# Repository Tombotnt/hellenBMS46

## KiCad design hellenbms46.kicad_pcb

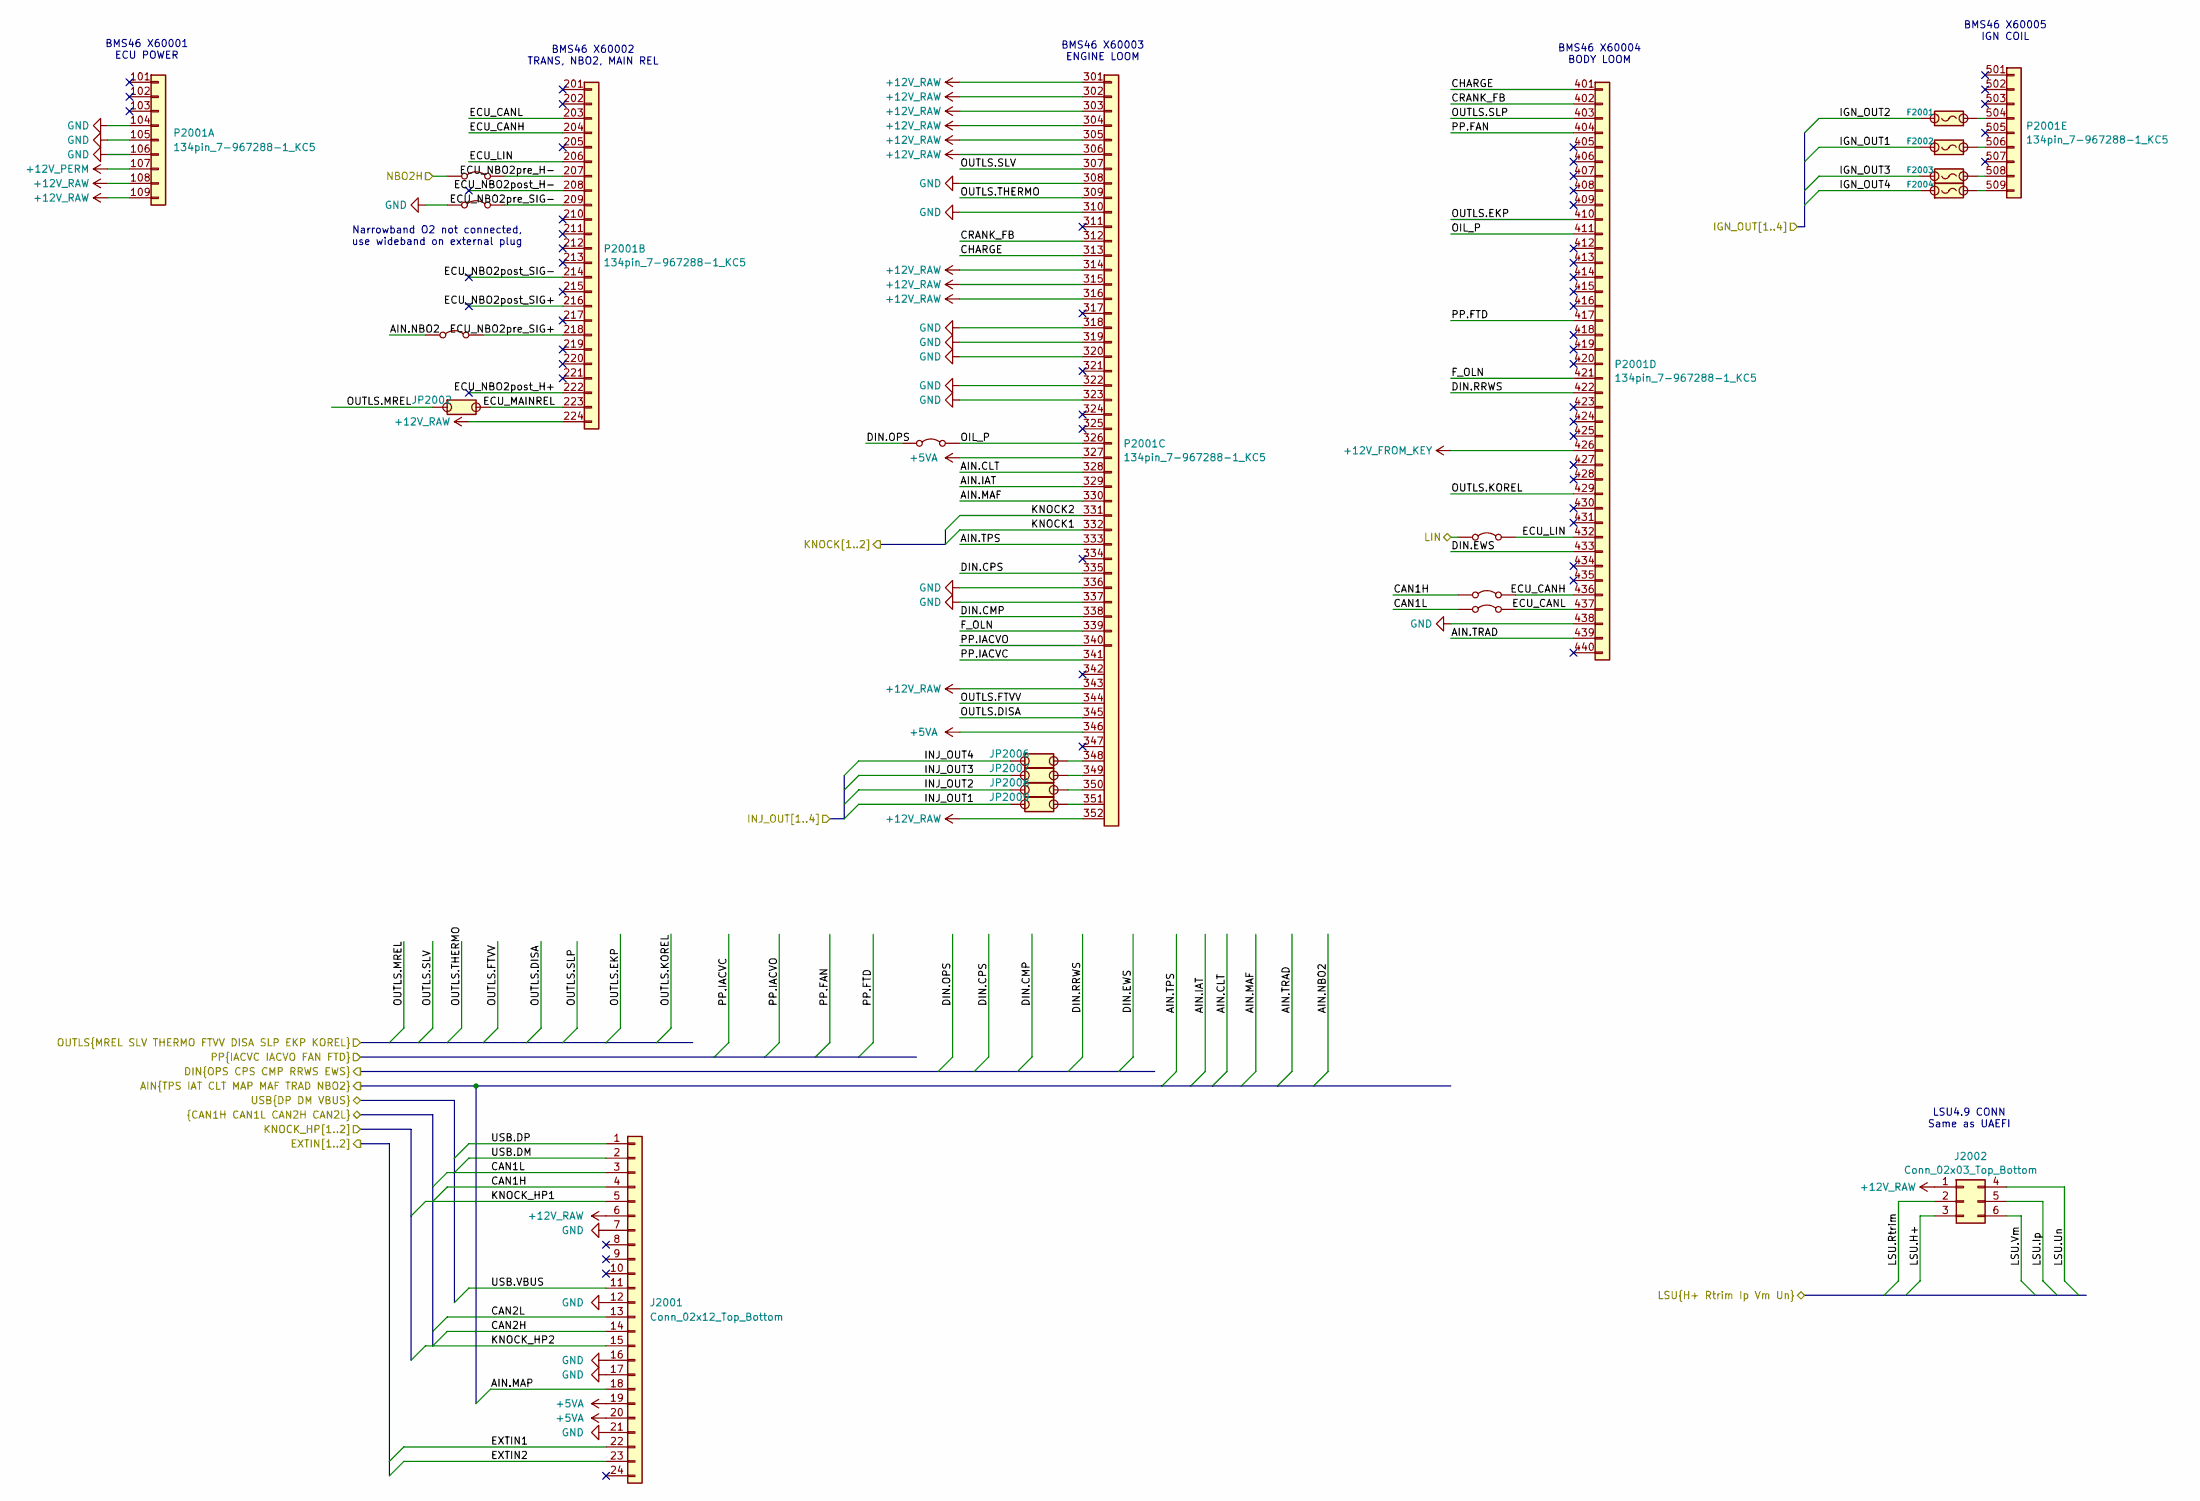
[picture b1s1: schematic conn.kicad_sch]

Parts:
F2001, F2002, F2003, F2004: 10A; 36911600000; LCSC C354908
J2001: Conn_02x12_Top_Bottom; 348260240
J2002: Conn_02x03_Top_Bottom; Molex_Mini-Fit_Jr_5569-06A2_2x03_P4.20mm_Horizontal
JP2001, JP2003, JP2004, JP2005, JP2010, JP2011, JP2012: Jumper_2_Bridged; SolderJumper-2_P1.3mm_Bridged_RoundedPad1.0x1.5mm
JP2002, JP2006, JP2007, JP2008, JP2009: Jumper_2_Open; PAD-0805-PAD; LCSC C17477
P2001: 134pin_7-967288-1_KC5; 7-967288-1_134-pin-connector

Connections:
+5VA: J2001.19, J2001.20, P2001.327, P2001.346; also elsewhere on the board
+12V_FROM_KEY: P2001.426; also elsewhere on the board
+12V_PERM: P2001.107; also elsewhere on the board
+12V_RAW: J2001.6, J2002.1, P2001.108, P2001.109, P2001.224, P2001.301, P2001.302, P2001.303, P2001.304, P2001.305, P2001.306, P2001.314, P2001.315, P2001.316, P2001.343, P2001.352; also elsewhere on the board
/conn/CHARGE: P2001.313, P2001.401
/conn/CRANK_FB: P2001.312, P2001.402
/conn/ECU_CANH: JP2011.2 (B), P2001.204, P2001.436
/conn/ECU_CANL: JP2012.2 (B), P2001.203, P2001.437
/conn/ECU_LIN: JP2010.2 (B), P2001.206, P2001.432
/conn/ECU_MAINREL: JP2002.2, P2001.223
/conn/ECU_NBO2post_H+: P2001.222
/conn/ECU_NBO2post_H-: P2001.208
/conn/ECU_NBO2post_SIG+: P2001.216
/conn/ECU_NBO2post_SIG-: P2001.214
/conn/ECU_NBO2pre_H-: JP2003.2 (B), P2001.207
/conn/ECU_NBO2pre_SIG+: JP2001.2 (B), P2001.218
/conn/ECU_NBO2pre_SIG-: JP2004.2 (B), P2001.209
/conn/EXTIN1: J2001.22; also elsewhere on the board
/conn/EXTIN2: J2001.23; also elsewhere on the board
/conn/F_OLN: P2001.339, P2001.421
/conn/IGN_OUT1: F2002.1; also elsewhere on the board
/conn/IGN_OUT2: F2001.1; also elsewhere on the board
/conn/IGN_OUT3: F2003.1; also elsewhere on the board
/conn/IGN_OUT4: F2004.1; also elsewhere on the board
/conn/INJ_OUT1: JP2009.1; also elsewhere on the board
/conn/INJ_OUT2: JP2008.1; also elsewhere on the board
/conn/INJ_OUT3: JP2007.1; also elsewhere on the board
/conn/INJ_OUT4: JP2006.1; also elsewhere on the board
/conn/KNOCK1: P2001.332; also elsewhere on the board
/conn/KNOCK2: P2001.331; also elsewhere on the board
/conn/OIL_P: JP2005.2 (B), P2001.326, P2001.411
/conn/OUTLS.DISA: P2001.345; also elsewhere on the board
/conn/OUTLS.EKP: P2001.410; also elsewhere on the board
/conn/OUTLS.FTVV: P2001.344; also elsewhere on the board
/conn/OUTLS.KOREL: P2001.429; also elsewhere on the board
/conn/OUTLS.MREL: JP2002.1; also elsewhere on the board
/conn/OUTLS.SLP: P2001.403; also elsewhere on the board
/conn/OUTLS.SLV: P2001.307; also elsewhere on the board
/conn/OUTLS.THERMO: P2001.309; also elsewhere on the board
/conn/PP.FAN: P2001.404; also elsewhere on the board
/conn/PP.FTD: P2001.417; also elsewhere on the board
/conn/PP.IACVC: P2001.341; also elsewhere on the board
/conn/PP.IACVO: P2001.340; also elsewhere on the board
/rusefi/AIN.CLT: P2001.328; also elsewhere on the board
/rusefi/AIN.IAT: P2001.329; also elsewhere on the board
/rusefi/AIN.MAF: P2001.330; also elsewhere on the board
/rusefi/AIN.MAP: J2001.18; also elsewhere on the board
/rusefi/AIN.NBO2: JP2001.1 (A); also elsewhere on the board
/rusefi/AIN.TPS: P2001.333; also elsewhere on the board
/rusefi/AIN.TRAD: P2001.439; also elsewhere on the board
/rusefi/CAN1H: J2001.4, JP2011.1 (A); also elsewhere on the board
/rusefi/CAN1L: J2001.3, JP2012.1 (A); also elsewhere on the board
/rusefi/CAN2H: J2001.14; also elsewhere on the board
/rusefi/CAN2L: J2001.13; also elsewhere on the board
/rusefi/DIN.CMP: P2001.338; also elsewhere on the board
/rusefi/DIN.CPS: P2001.335; also elsewhere on the board
/rusefi/DIN.EWS: P2001.433; also elsewhere on the board
/rusefi/DIN.OPS: JP2005.1 (A); also elsewhere on the board
/rusefi/DIN.RRWS: P2001.422; also elsewhere on the board
/rusefi/KnockAmps/KNOCK_HP1: J2001.5; also elsewhere on the board
/rusefi/KnockAmps/KNOCK_HP2: J2001.15; also elsewhere on the board
/rusefi/LIN: JP2010.1 (A); also elsewhere on the board
/rusefi/LSU.H+: J2002.3; also elsewhere on the board
/rusefi/LSU.Ip: J2002.5; also elsewhere on the board
/rusefi/LSU.Rtrim: J2002.2; also elsewhere on the board
/rusefi/LSU.Un: J2002.4; also elsewhere on the board
/rusefi/LSU.Vm: J2002.6; also elsewhere on the board
/rusefi/NBO2H: JP2003.1 (A); also elsewhere on the board
/rusefi/USB.DM: J2001.2; also elsewhere on the board
/rusefi/USB.DP: J2001.1; also elsewhere on the board
/rusefi/USB.VBUS: J2001.11; also elsewhere on the board
GND: J2001.7, J2001.12, J2001.16, J2001.17, J2001.21, JP2004.1 (A), P2001.104, P2001.105, P2001.106, P2001.308, P2001.310, P2001.318, P2001.319, P2001.320, P2001.322, P2001.323, P2001.336, P2001.337, P2001.438; also elsewhere on the board
unnamed: JP2006.2, P2001.348
unnamed: JP2007.2, P2001.349
unnamed: JP2008.2, P2001.350
unnamed: JP2009.2, P2001.351
unnamed: F2001.2, P2001.504
unnamed: F2002.2, P2001.506
unnamed: F2003.2, P2001.508
unnamed: F2004.2, P2001.509

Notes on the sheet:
BMS46 X60003 ENGINE LOOM
LSU4.9 CONN Same as UAEFI
BMS46 X60005 IGN COIL
BMS46 X60002 TRANS, NBO2, MAIN REL
Narrowband O2 not connected, use wideband on external plug
BMS46 X60001 ECU POWER
BMS46 X60004 BODY LOOM

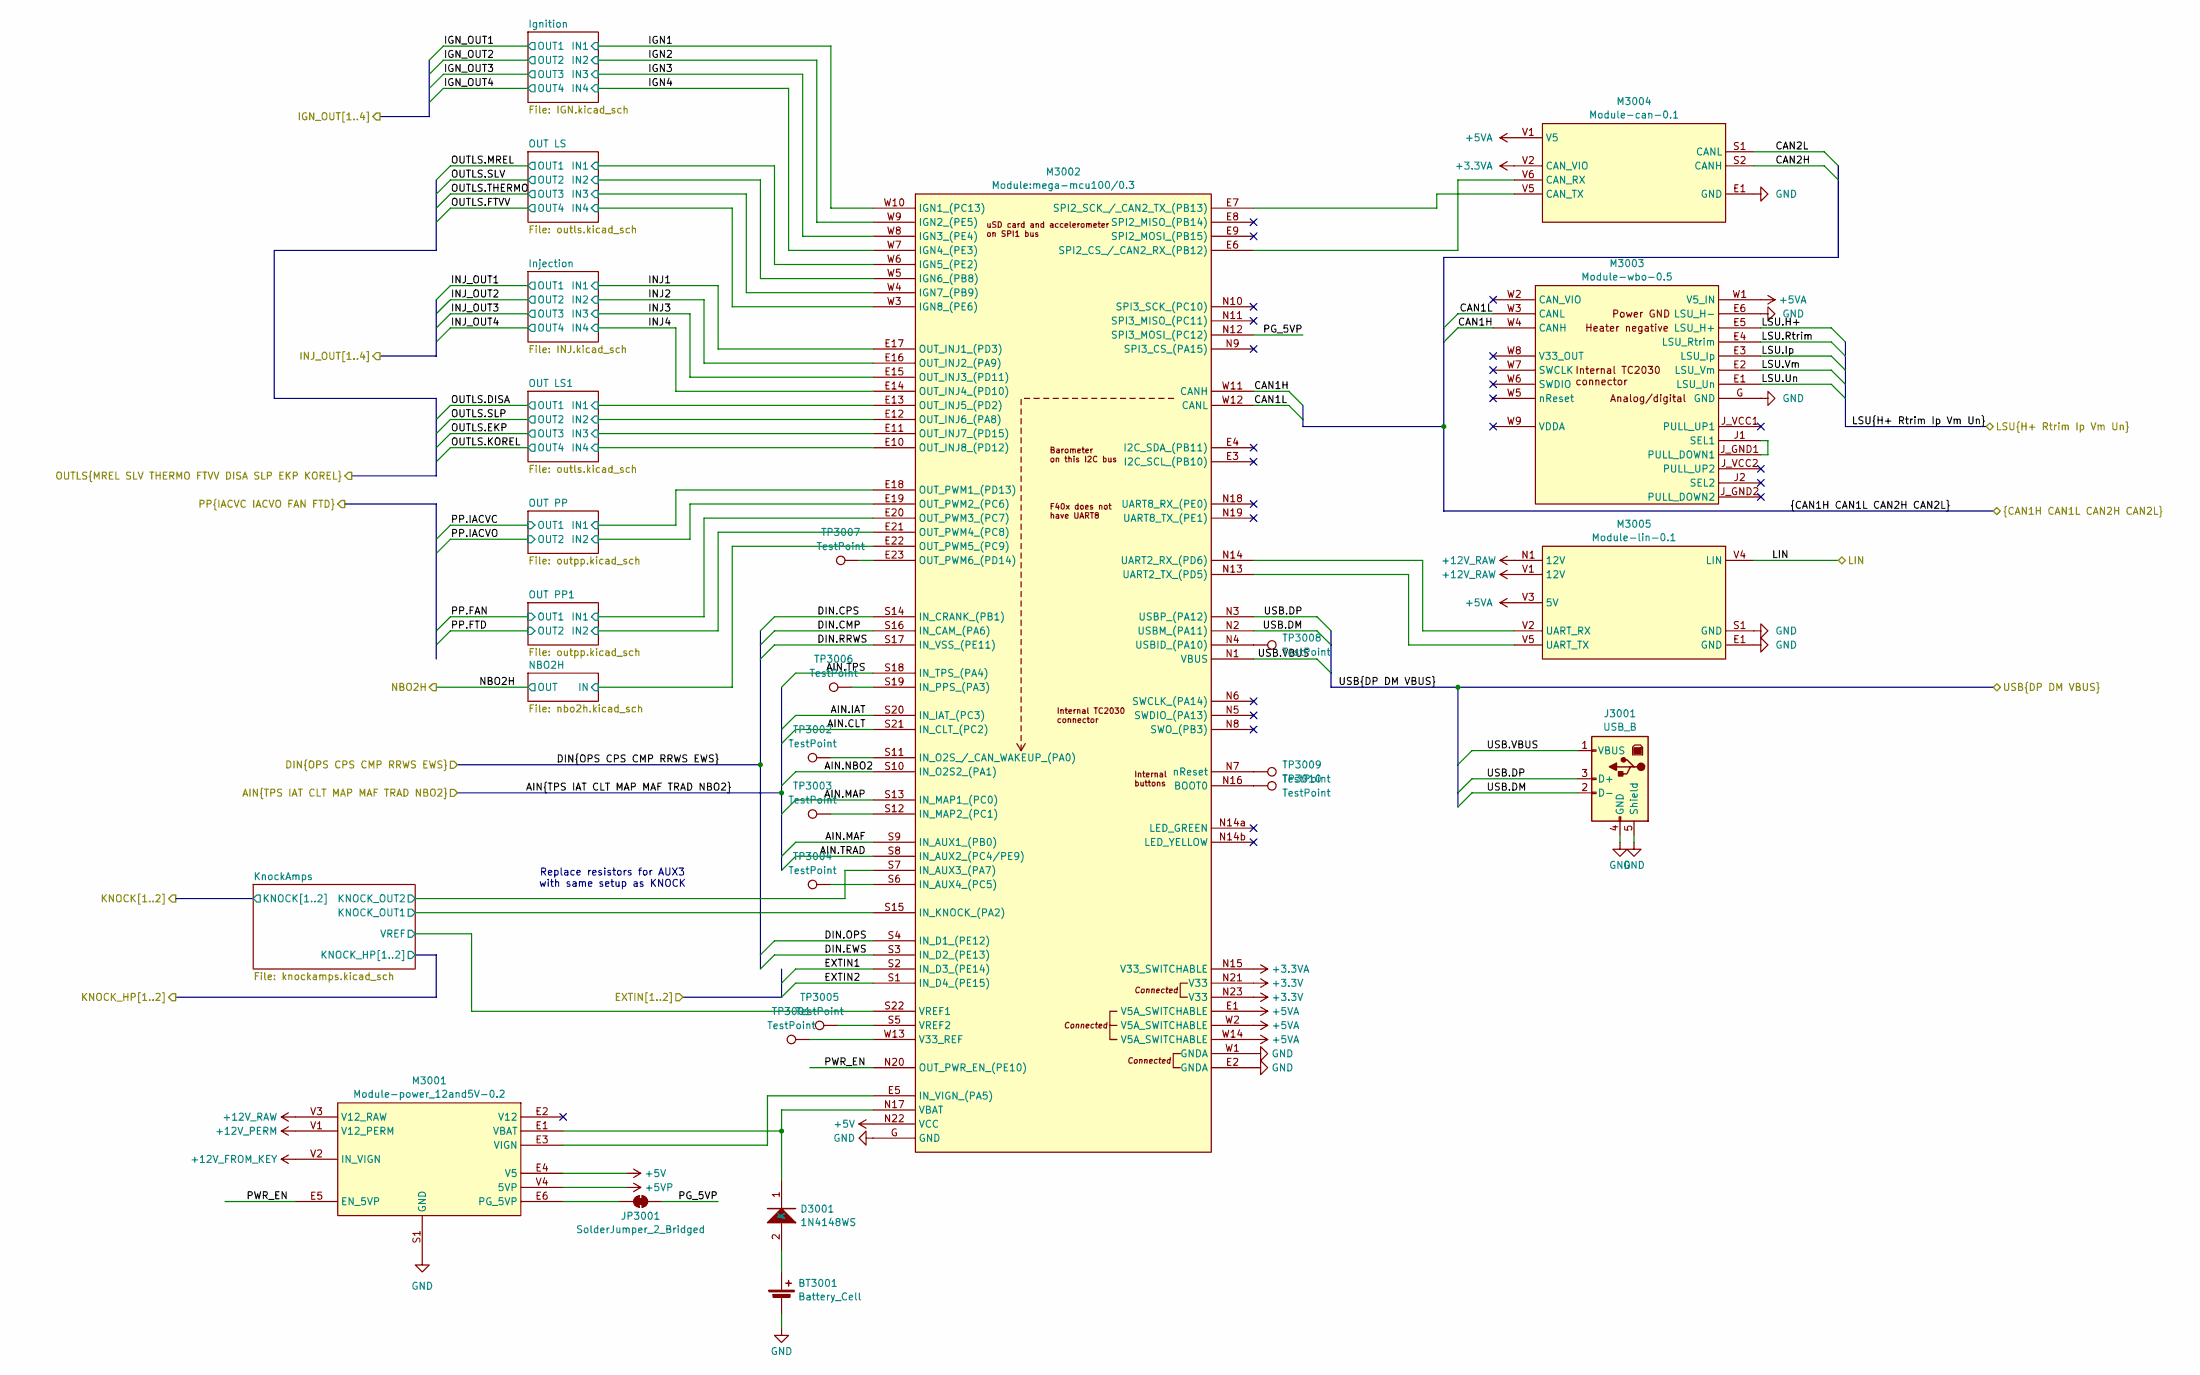
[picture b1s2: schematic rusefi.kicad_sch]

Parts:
BT3001: Battery_Cell; BatteryHolder_Keystone_1058_1x2032
D3001: 1N4148WS; SOD-323; LCSC C2128
J3001: USB_B; LCSC C46392
JP3001: SolderJumper_2_Bridged; SolderJumper-2_P1.3mm_Bridged_RoundedPad1.0x1.5mm
M3001: Module-power_12and5V-0.2; power_12and5V
M3002: Module:mega-mcu100/0.3; mega-mcu100
M3003: Module-wbo-0.5; wbo
M3004: Module-can-0.1; can
M3005: Module-lin-0.1; lin
TP3001, TP3002, TP3003, TP3004, TP3005, TP3006, TP3007, TP3008, TP3009, TP3010: TestPoint; TestPoint_Keystone_5000-5004_Miniature

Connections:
+3.3V: M3002.N21 (V33), M3002.N23 (V33)
+3.3VA: M3002.N15 (V33_SWITCHABLE), M3004.V2 (CAN_VIO)
+5V: M3001.E4 (V5), M3002.N22 (VCC)
+5VA: M3002.E1 (V5A_SWITCHABLE), M3002.W2 (V5A_SWITCHABLE), M3002.W14 (V5A_SWITCHABLE), M3003.W1 (V5_IN), M3004.V1 (V5), M3005.V3 (5V); also elsewhere on the board
+5VP: M3001.V4 (5VP)
+12V_FROM_KEY: M3001.V2 (IN_VIGN); also elsewhere on the board
+12V_PERM: M3001.V1 (V12_PERM); also elsewhere on the board
+12V_RAW: M3001.V3 (V12_RAW), M3005.N1 (12V), M3005.V1 (12V); also elsewhere on the board
/conn/EXTIN1: M3002.S2 (IN_D3_(PE14)); also elsewhere on the board
/conn/EXTIN2: M3002.S1 (IN_D4_(PE15)); also elsewhere on the board
/rusefi/AIN.CLT: M3002.S21 (IN_CLT_(PC2)); also elsewhere on the board
/rusefi/AIN.IAT: M3002.S20 (IN_IAT_(PC3)); also elsewhere on the board
/rusefi/AIN.MAF: M3002.S9 (IN_AUX1_(PB0)); also elsewhere on the board
/rusefi/AIN.MAP: M3002.S13 (IN_MAP1_(PC0)); also elsewhere on the board
/rusefi/AIN.NBO2: M3002.S10 (IN_O2S2_(PA1)); also elsewhere on the board
/rusefi/AIN.TPS: M3002.S18 (IN_TPS_(PA4)); also elsewhere on the board
/rusefi/AIN.TRAD: M3002.S8 (IN_AUX2_(PC4/PE9)); also elsewhere on the board
/rusefi/CAN1H: M3002.W11 (CANH), M3003.W4 (CANH); also elsewhere on the board
/rusefi/CAN1L: M3002.W12 (CANL), M3003.W3 (CANL); also elsewhere on the board
/rusefi/CAN2H: M3004.S2 (CANH); also elsewhere on the board
/rusefi/CAN2L: M3004.S1 (CANL); also elsewhere on the board
/rusefi/DIN.CMP: M3002.S16 (IN_CAM_(PA6)); also elsewhere on the board
/rusefi/DIN.CPS: M3002.S14 (IN_CRANK_(PB1)); also elsewhere on the board
/rusefi/DIN.EWS: M3002.S3 (IN_D2_(PE13)); also elsewhere on the board
/rusefi/DIN.OPS: M3002.S4 (IN_D1_(PE12)); also elsewhere on the board
/rusefi/DIN.RRWS: M3002.S17 (IN_VSS_(PE11)); also elsewhere on the board
/rusefi/IGN1: M3002.W10 (IGN1_(PC13)); also elsewhere on the board
/rusefi/IGN2: M3002.W9 (IGN2_(PE5)); also elsewhere on the board
/rusefi/IGN3: M3002.W8 (IGN3_(PE4)); also elsewhere on the board
/rusefi/IGN4: M3002.W7 (IGN4_(PE3)); also elsewhere on the board
/rusefi/INJ1: M3002.E17 (OUT_INJ1_(PD3)); also elsewhere on the board
/rusefi/INJ2: M3002.E16 (OUT_INJ2_(PA9)); also elsewhere on the board
/rusefi/INJ3: M3002.E15 (OUT_INJ3_(PD11)); also elsewhere on the board
/rusefi/INJ4: M3002.E14 (OUT_INJ4_(PD10)); also elsewhere on the board
/rusefi/KnockAmps/KNOCK_OUT1: M3002.S15 (IN_KNOCK_(PA2)); also elsewhere on the board
/rusefi/KnockAmps/KNOCK_OUT2: M3002.S7 (IN_AUX3_(PA7)); also elsewhere on the board
/rusefi/KnockAmps/VREF: M3002.S22 (VREF1); also elsewhere on the board
/rusefi/LIN: M3005.V4 (LIN); also elsewhere on the board
/rusefi/LSU.H+: M3003.E5 (LSU_H+); also elsewhere on the board
/rusefi/LSU.Ip: M3003.E3 (LSU_Ip); also elsewhere on the board
/rusefi/LSU.Rtrim: M3003.E4 (LSU_Rtrim); also elsewhere on the board
/rusefi/LSU.Un: M3003.E1 (LSU_Un); also elsewhere on the board
/rusefi/LSU.Vm: M3003.E2 (LSU_Vm); also elsewhere on the board
/rusefi/NBO2H/IN: M3002.E22 (OUT_PWM5_(PC9)); also elsewhere on the board
/rusefi/OUT LS1/IN1: M3002.E13 (OUT_INJ5_(PD2)); also elsewhere on the board
/rusefi/OUT LS1/IN2: M3002.E12 (OUT_INJ6_(PA8)); also elsewhere on the board
/rusefi/OUT LS1/IN3: M3002.E11 (OUT_INJ7_(PD15)); also elsewhere on the board
/rusefi/OUT LS1/IN4: M3002.E10 (OUT_INJ8_(PD12)); also elsewhere on the board
/rusefi/OUT LS/IN1: M3002.W6 (IGN5_(PE2)); also elsewhere on the board
/rusefi/OUT LS/IN2: M3002.W5 (IGN6_(PB8)); also elsewhere on the board
/rusefi/OUT LS/IN3: M3002.W4 (IGN7_(PB9)); also elsewhere on the board
/rusefi/OUT LS/IN4: M3002.W3 (IGN8_(PE6)); also elsewhere on the board
/rusefi/OUT PP1/IN1: M3002.E20 (OUT_PWM3_(PC7)); also elsewhere on the board
/rusefi/OUT PP1/IN2: M3002.E21 (OUT_PWM4_(PC8)); also elsewhere on the board
/rusefi/OUT PP/IN1: M3002.E18 (OUT_PWM1_(PD13)); also elsewhere on the board
/rusefi/OUT PP/IN2: M3002.E19 (OUT_PWM2_(PC6)); also elsewhere on the board
/rusefi/PG_5VP: JP3001.2 (B), M3002.N12 (SPI3_MOSI_(PC12))
/rusefi/PWR_EN: M3001.E5 (EN_5VP), M3002.N20 (OUT_PWR_EN_(PE10))
/rusefi/USB.DM: J3001.2 (D-), M3002.N2 (USBM_(PA11)); also elsewhere on the board
/rusefi/USB.DP: J3001.3 (D+), M3002.N3 (USBP_(PA12)); also elsewhere on the board
/rusefi/USB.VBUS: J3001.1 (VBUS), M3002.N1 (VBUS); also elsewhere on the board
GND: BT3001.2 (-), J3001.4 (GND), J3001.5 (Shield), M3001.S1 (GND), M3002.E2 (GNDA), M3002.G (GND), M3002.W1 (GNDA), M3003.E6 (LSU_H-), M3003.G (GND), M3004.E1 (GND), M3005.E1 (GND), M3005.S1 (GND); also elsewhere on the board
unnamed: BT3001.1 (+), D3001.2 (A)
unnamed: D3001.1 (K), M3001.E1 (VBAT), M3002.N17 (VBAT)
unnamed: JP3001.1 (A), M3001.E6 (PG_5VP)
unnamed: M3001.E3 (VIGN), M3002.E5 (IN_VIGN_(PA5))
unnamed: M3002.N16 (BOOT0), TP3010.1
unnamed: M3002.S6 (IN_AUX4_(PC5)), TP3004.1
unnamed: M3002.S12 (IN_MAP2_(PC1)), TP3003.1
unnamed: M3002.S11 (IN_O2S_/_CAN_WAKEUP_(PA0)), TP3002.1
unnamed: M3002.S19 (IN_PPS_(PA3)), TP3006.1
unnamed: M3002.E23 (OUT_PWM6_(PD14)), TP3007.1
unnamed: M3002.E6 (SPI2_CS_/_CAN2_RX_(PB12)), M3004.V6 (CAN_RX)
unnamed: M3002.E7 (SPI2_SCK_/_CAN2_TX_(PB13)), M3004.V5 (CAN_TX)
unnamed: M3002.N14 (UART2_RX_(PD6)), M3005.V2 (UART_RX)
unnamed: M3002.N13 (UART2_TX_(PD5)), M3005.V5 (UART_TX)
unnamed: M3002.N4 (USBID_(PA10)), TP3008.1
unnamed: M3002.W13 (V33_REF), TP3001.1
unnamed: M3002.S5 (VREF2), TP3005.1
unnamed: M3002.N7 (nReset), TP3009.1
unnamed: M3003.J1 (SEL1), M3003.J_GND1 (PULL_DOWN1)

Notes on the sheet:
Replace resistors for AUX3 with same setup as KNOCK

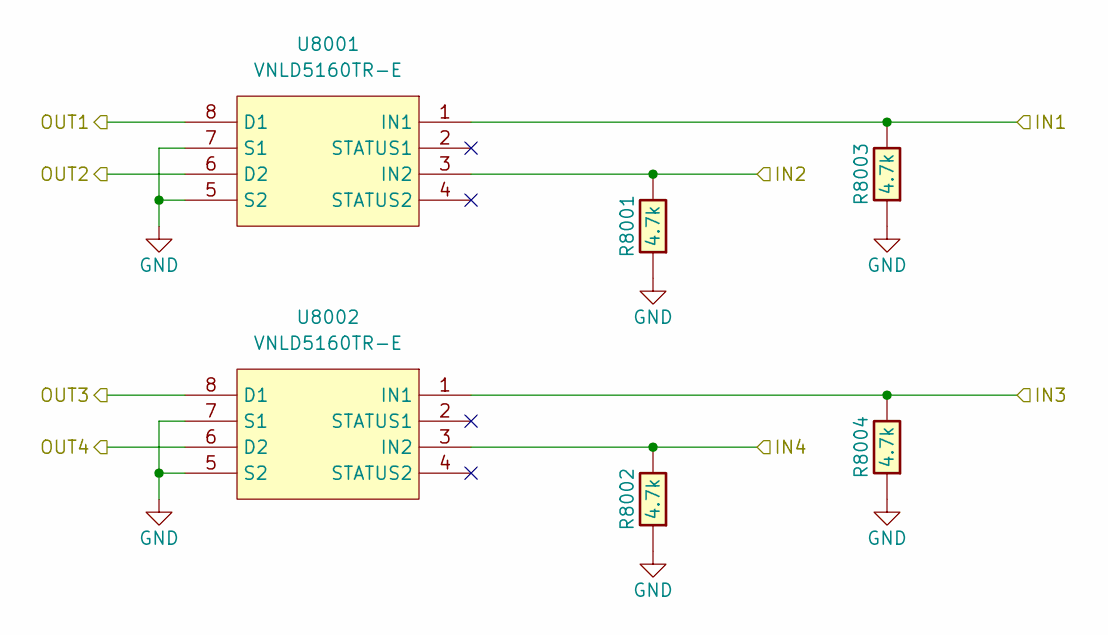
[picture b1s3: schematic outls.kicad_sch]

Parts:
R8001, R8002, R8003, R8004: 4.7k; R0603; LCSC C23162
U8001, U8002: VNLD5160TR-E; SOIC-8_3.9x4.9mm_P1.27mm; LCSC C377942

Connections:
/conn/OUTLS.DISA: U8001.8 (D1); also elsewhere on the board
/conn/OUTLS.EKP: U8002.8 (D1); also elsewhere on the board
/conn/OUTLS.KOREL: U8002.6 (D2); also elsewhere on the board
/conn/OUTLS.SLP: U8001.6 (D2); also elsewhere on the board
/rusefi/OUT LS1/IN1: R8003.2, U8001.1 (IN1); also elsewhere on the board
/rusefi/OUT LS1/IN2: R8001.2, U8001.3 (IN2); also elsewhere on the board
/rusefi/OUT LS1/IN3: R8004.2, U8002.1 (IN1); also elsewhere on the board
/rusefi/OUT LS1/IN4: R8002.2, U8002.3 (IN2); also elsewhere on the board
GND: R8001.1, R8002.1, R8003.1, R8004.1, U8001.5 (S2), U8001.7 (S1), U8002.5 (S2), U8002.7 (S1); also elsewhere on the board

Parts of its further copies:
R7001, R7002, R7003, R7004: 4.7k; R0603; LCSC C23162
U7001, U7002: VNLD5160TR-E; SOIC-8_3.9x4.9mm_P1.27mm; LCSC C377942

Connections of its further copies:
/conn/OUTLS.FTVV: U7002.6 (D2); also elsewhere on the board
/conn/OUTLS.MREL: U7001.8 (D1); also elsewhere on the board
/conn/OUTLS.SLV: U7001.6 (D2); also elsewhere on the board
/conn/OUTLS.THERMO: U7002.8 (D1); also elsewhere on the board
/rusefi/OUT LS/IN1: R7003.2, U7001.1 (IN1); also elsewhere on the board
/rusefi/OUT LS/IN2: R7001.2, U7001.3 (IN2); also elsewhere on the board
/rusefi/OUT LS/IN3: R7004.2, U7002.1 (IN1); also elsewhere on the board
/rusefi/OUT LS/IN4: R7002.2, U7002.3 (IN2); also elsewhere on the board
GND: R7001.1, R7002.1, R7003.1, R7004.1, U7001.5 (S2), U7001.7 (S1), U7002.5 (S2), U7002.7 (S1); also elsewhere on the board

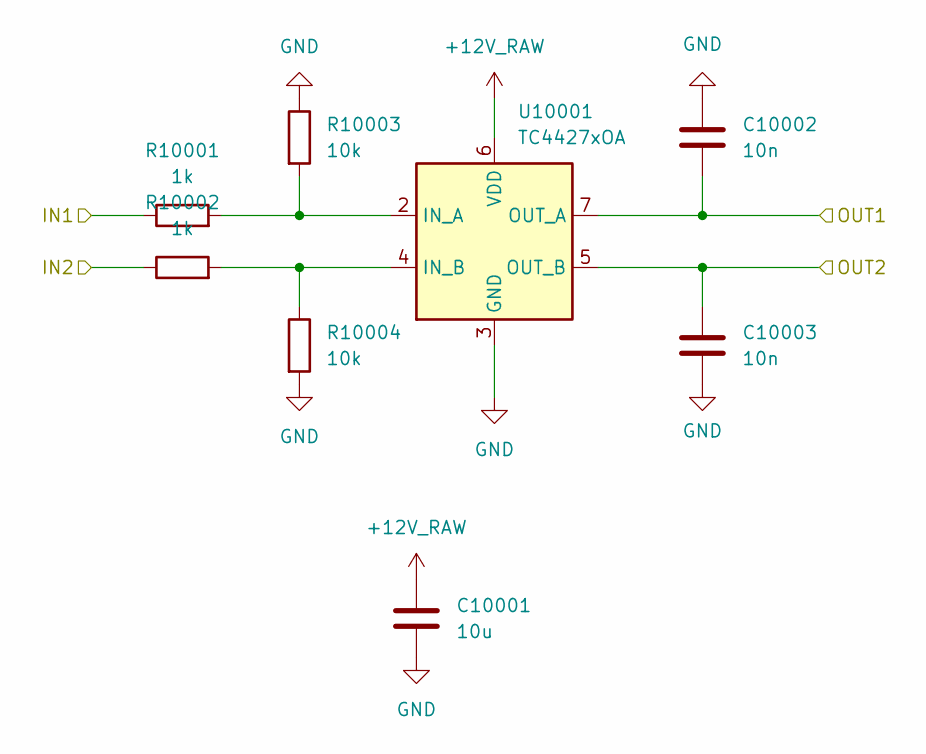
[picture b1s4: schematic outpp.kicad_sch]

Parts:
C10001: 10u; C0805; LCSC C440198
C10002, C10003: 10n; C0805; LCSC C597285
R10001, R10002: 1k; R0603; LCSC C21190
R10003, R10004: 10k; R0603; LCSC C98220
U10001: TC4427xOA; SOIC-8_3.9x4.9mm_P1.27mm; LCSC C636893

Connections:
+12V_RAW: C10001.1, U10001.6 (VDD); also elsewhere on the board
/conn/PP.FAN: C10002.2, U10001.7 (OUT_A); also elsewhere on the board
/conn/PP.FTD: C10003.1, U10001.5 (OUT_B); also elsewhere on the board
/rusefi/OUT PP1/IN1: R10001.1; also elsewhere on the board
/rusefi/OUT PP1/IN2: R10002.1; also elsewhere on the board
GND: C10001.2, C10002.1, C10003.2, R10003.1, R10004.2, U10001.3 (GND); also elsewhere on the board
unnamed: R10001.2, R10003.2, U10001.2 (IN_A)
unnamed: R10002.2, R10004.1, U10001.4 (IN_B)

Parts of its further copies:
C9001: 10u; C0805; LCSC C440198
C9002, C9003: 10n; C0805; LCSC C597285
R9001, R9002: 1k; R0603; LCSC C21190
R9003, R9004: 10k; R0603; LCSC C98220
U9001: TC4427xOA; SOIC-8_3.9x4.9mm_P1.27mm; LCSC C636893

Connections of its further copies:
+12V_RAW: C9001.1, U9001.6 (VDD); also elsewhere on the board
/conn/PP.IACVC: C9002.2, U9001.7 (OUT_A); also elsewhere on the board
/conn/PP.IACVO: C9003.1, U9001.5 (OUT_B); also elsewhere on the board
/rusefi/OUT PP/IN1: R9001.1; also elsewhere on the board
/rusefi/OUT PP/IN2: R9002.1; also elsewhere on the board
GND: C9001.2, C9002.1, C9003.2, R9003.1, R9004.2, U9001.3 (GND); also elsewhere on the board
unnamed: R9001.2, R9003.2, U9001.2 (IN_A)
unnamed: R9002.2, R9004.1, U9001.4 (IN_B)

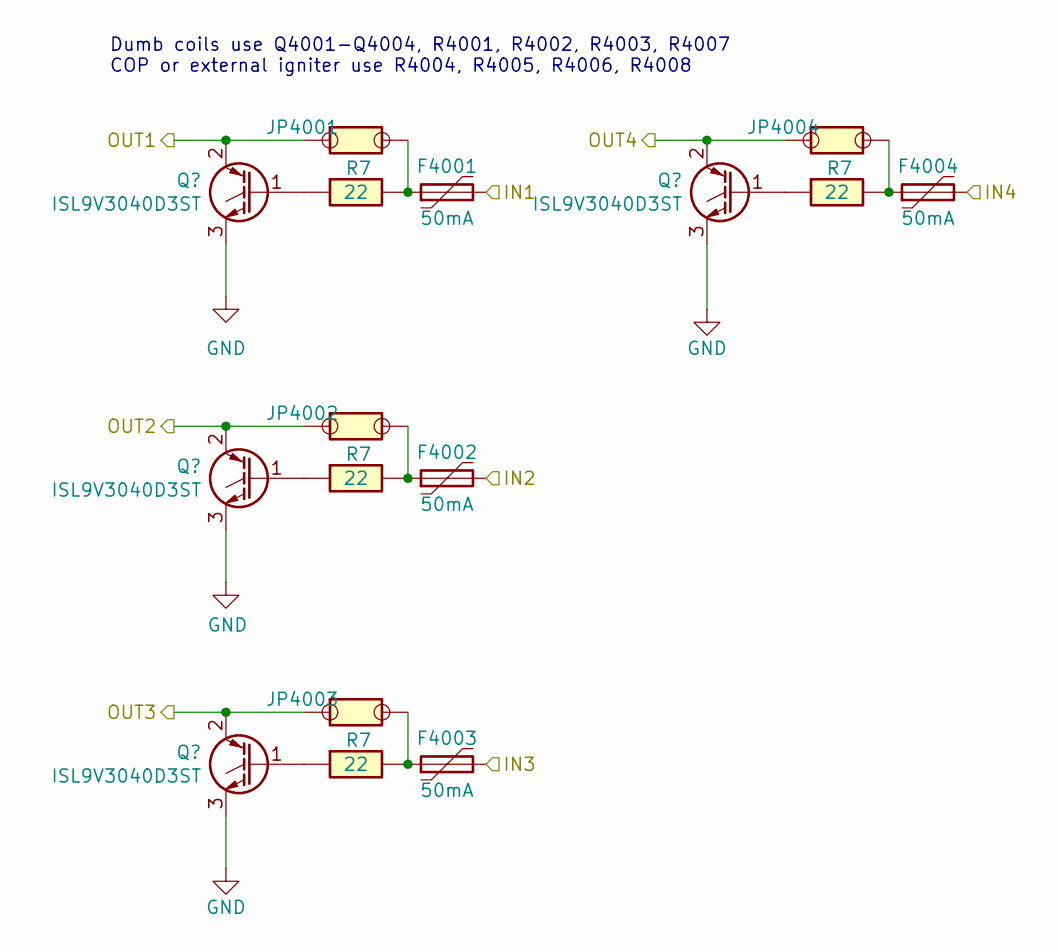
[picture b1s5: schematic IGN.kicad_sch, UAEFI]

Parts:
F4001, F4002, F4003, F4004: 50mA; Fuse_0603_1608Metric; LCSC C369141
JP4001, JP4002, JP4003, JP4004: Jumper_2_Open; PAD-0805-PAD; LCSC C17477
Q4001, Q4002, Q4003, Q4004: ISL9V3040D3ST; TO-252-2; LCSC C462128
R7: 22; R0603; LCSC C23345

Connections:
/conn/IGN_OUT1: JP4001.1, Q4001.2 (C); also elsewhere on the board
/conn/IGN_OUT2: JP4002.1, Q4002.2 (C); also elsewhere on the board
/conn/IGN_OUT3: JP4003.1, Q4003.2 (C); also elsewhere on the board
/conn/IGN_OUT4: JP4004.1, Q4004.2 (C); also elsewhere on the board
/rusefi/IGN1: F4001.2; also elsewhere on the board
/rusefi/IGN2: F4002.2; also elsewhere on the board
/rusefi/IGN3: F4003.2; also elsewhere on the board
/rusefi/IGN4: F4004.2; also elsewhere on the board
GND: Q4001.3 (E), Q4002.3 (E), Q4003.3 (E), Q4004.3 (E); also elsewhere on the board
unnamed 104: F4001.1, JP4001.2; also elsewhere on the board
unnamed 105: F4002.1, JP4002.2; also elsewhere on the board
unnamed 106: F4003.1, JP4003.2; also elsewhere on the board
unnamed 107: F4004.1, JP4004.2; also elsewhere on the board
unnamed 134: Q4001.1 (G); also elsewhere on the board
unnamed 135: Q4002.1 (G); also elsewhere on the board
unnamed 136: Q4003.1 (G); also elsewhere on the board
unnamed 137: Q4004.1 (G); also elsewhere on the board

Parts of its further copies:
R4001, R4002, R4003, R4004: 22; R0603; LCSC C23345

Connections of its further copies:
unnamed 104: R4001.2; also elsewhere on the board
unnamed 105: R4002.2; also elsewhere on the board
unnamed 106: R4003.2; also elsewhere on the board
unnamed 107: R4004.2; also elsewhere on the board
unnamed 134: R4001.1; also elsewhere on the board
unnamed 135: R4002.1; also elsewhere on the board
unnamed 136: R4003.1; also elsewhere on the board
unnamed 137: R4004.1; also elsewhere on the board

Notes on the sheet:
Dumb coils use Q4001-Q4004, R4001, R4002, R4003, R4007 COP or external igniter use R4004, R4005, R4006, R4008

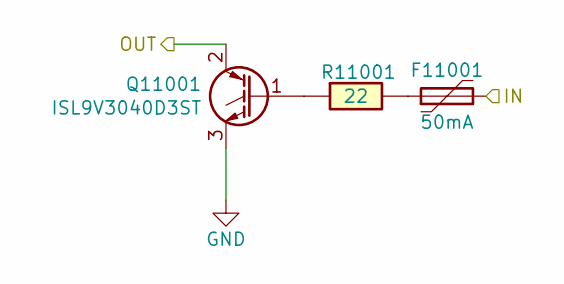
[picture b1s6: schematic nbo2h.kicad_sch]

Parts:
F11001: 50mA; Fuse_0603_1608Metric; LCSC C369141
Q11001: ISL9V3040D3ST; TO-252-2; LCSC C462128
R11001: 22; R0603; LCSC C23345

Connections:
/rusefi/NBO2H: Q11001.2 (C); also elsewhere on the board
/rusefi/NBO2H/IN: F11001.2; also elsewhere on the board
GND: Q11001.3 (E); also elsewhere on the board
unnamed: F11001.1, R11001.2
unnamed: Q11001.1 (G), R11001.1

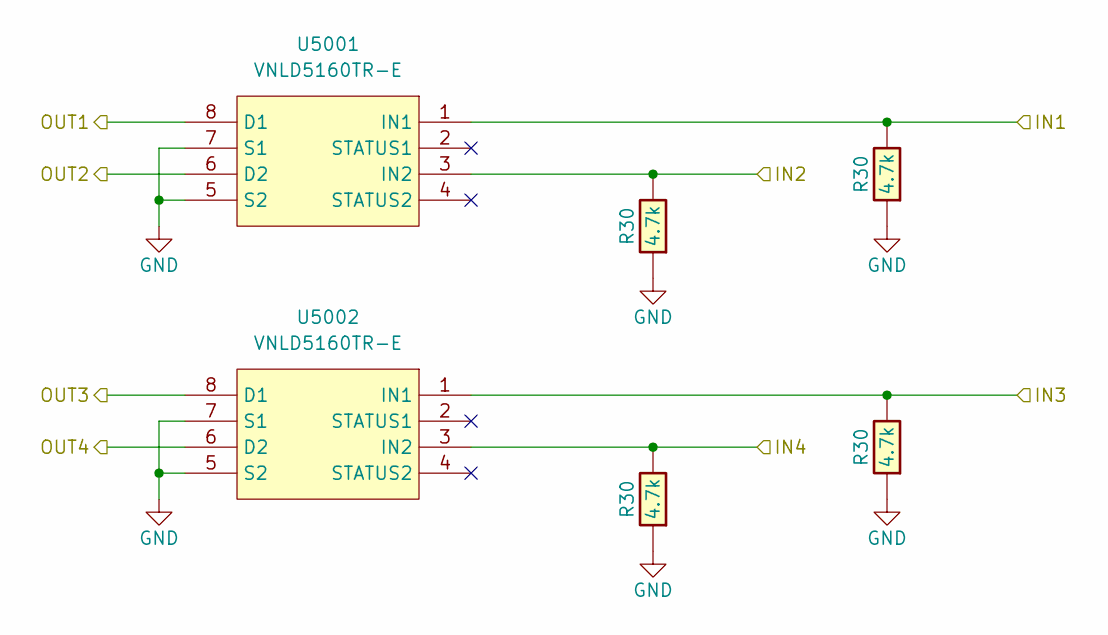
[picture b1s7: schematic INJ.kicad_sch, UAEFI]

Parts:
R30: 4.7k; R0603; LCSC C23162
U5001, U5002: VNLD5160TR-E; SOIC-8_3.9x4.9mm_P1.27mm; LCSC C377942

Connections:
/conn/INJ_OUT1: U5001.8 (D1); also elsewhere on the board
/conn/INJ_OUT2: U5001.6 (D2); also elsewhere on the board
/conn/INJ_OUT3: U5002.8 (D1); also elsewhere on the board
/conn/INJ_OUT4: U5002.6 (D2); also elsewhere on the board
/rusefi/INJ1: U5001.1 (IN1); also elsewhere on the board
/rusefi/INJ2: U5001.3 (IN2); also elsewhere on the board
/rusefi/INJ3: U5002.1 (IN1); also elsewhere on the board
/rusefi/INJ4: U5002.3 (IN2); also elsewhere on the board
GND: U5001.5 (S2), U5001.7 (S1), U5002.5 (S2), U5002.7 (S1); also elsewhere on the board

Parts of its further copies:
R5001, R5002, R5003, R5004: 4.7k; R0603; LCSC C23162

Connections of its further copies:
/rusefi/INJ1: R5003.2; also elsewhere on the board
/rusefi/INJ2: R5001.2; also elsewhere on the board
/rusefi/INJ3: R5004.2; also elsewhere on the board
/rusefi/INJ4: R5002.2; also elsewhere on the board
GND: R5001.1, R5002.1, R5003.1, R5004.1; also elsewhere on the board

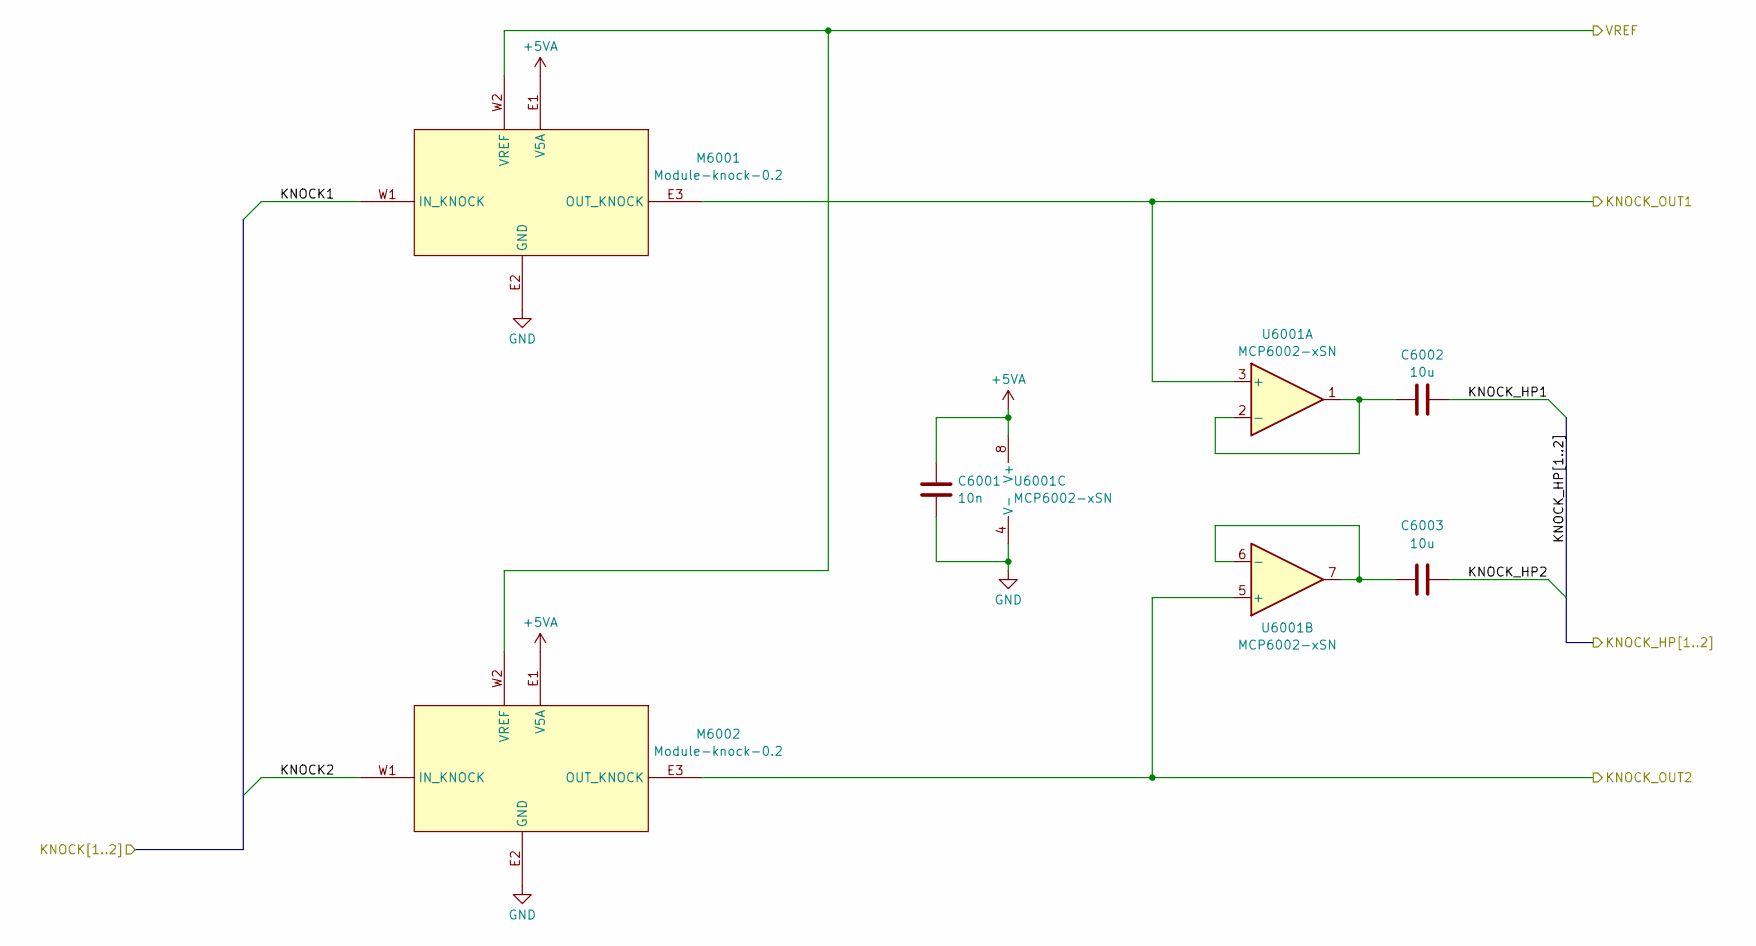
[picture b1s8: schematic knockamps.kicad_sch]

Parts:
C6001: 10n; C0805; LCSC C597285
C6002, C6003: 10u; C0805; LCSC C440198
M6001, M6002: Module-knock-0.2; knock
U6001: MCP6002-xSN; SOIC-8_3.9x4.9mm_P1.27mm; LCSC C636235

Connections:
+5VA: C6001.1, M6001.E1 (V5A), M6002.E1 (V5A), U6001.8 (V+); also elsewhere on the board
/conn/KNOCK1: M6001.W1 (IN_KNOCK); also elsewhere on the board
/conn/KNOCK2: M6002.W1 (IN_KNOCK); also elsewhere on the board
/rusefi/KnockAmps/KNOCK_HP1: C6002.2; also elsewhere on the board
/rusefi/KnockAmps/KNOCK_HP2: C6003.2; also elsewhere on the board
/rusefi/KnockAmps/KNOCK_OUT1: M6001.E3 (OUT_KNOCK), U6001.3 (+); also elsewhere on the board
/rusefi/KnockAmps/KNOCK_OUT2: M6002.E3 (OUT_KNOCK), U6001.5 (+); also elsewhere on the board
/rusefi/KnockAmps/VREF: M6001.W2 (VREF), M6002.W2 (VREF); also elsewhere on the board
GND: C6001.2, M6001.E2 (GND), M6002.E2 (GND), U6001.4 (V-); also elsewhere on the board
unnamed: C6002.1, U6001.1, U6001.2 (-)
unnamed: C6003.1, U6001.6 (-), U6001.7

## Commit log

2025-02-16 inital commit
2025-02-16 test commit
2025-02-16 [skip actions] Auto-generated board v2.1
2025-02-16 fixed bom_replace filename
2025-02-20 Initial schematic
2025-02-20 inital schamatic
2025-02-20 adjusted BOM
2025-02-20 testsing
